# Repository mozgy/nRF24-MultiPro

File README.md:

# nRF24-MultiPro
nRF24 MultiPro

Adapter for nRF24 board and Arduino Pro Mini.
Firmware is at https://github.com/goebish/nrf24_multipro

# BOM
Qty|Part|Description|Value|Package|RS Part Number
---|----|-----------|-----|-------|-------------------
1|IC1|Voltage Regulator 3.3V|SPX3819 3.3|SOT23-5|
1|Q1|MOSFET|BSS123|SOT-23|
1|Q2|BJT|2N2222|SOT-23|
1|C1|Cap Tantalum|2.2uF/16V|3216|
2|R1,R2|SMD Resistor|10k|0805|
3|R3,R4,R5|SMD Resistor|1k|0805|
1|JP1|Pin Header|2x4|
2|JP2,JP3|Pin Header|1x12|
1|JP4|Molex Connector|1x5|

(C1 '+' cap markings are towards outter edge of the PCB)

Special thanks to excellent video by Jason Sanctuary - https://www.youtube.com/watch?v=gJYiDjo5lQw

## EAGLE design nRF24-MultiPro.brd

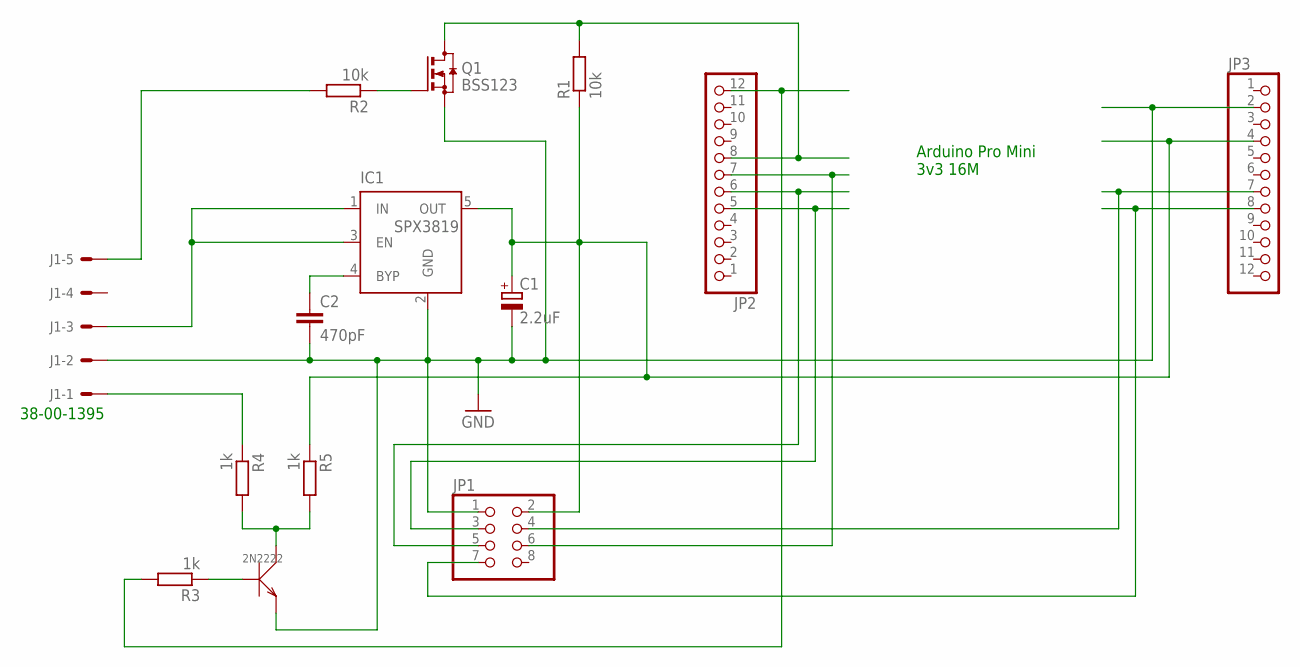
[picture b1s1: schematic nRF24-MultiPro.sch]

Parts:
2N2222: TRANSISTOR-NPN; SOT-23
C1: 2.2uF; A/3216-18W
C2: 470pF; C0805
IC1: SPX3819; SOT23-5
J1: 22-27-2051-05; 6410-05
JP1: PINHD-2X4; 2X04
JP2, JP3: PINHD-1X12; 1X12
Q1: BSS123; SOT23
R1, R2: 10k; R0805
R3, R4, R5: 1k; R0805

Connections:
GND: 2N2222.2 (E), C1.-, C2.2, IC1.2 (GND), J1.2, JP1.1, JP3.2, Q1.2 (S)
unnamed: IC1.1 (IN), IC1.3 (EN), J1.3
unnamed: JP2.8, Q1.3 (D), R1.2
unnamed: JP1.4, JP3.7
unnamed: C1.+, IC1.5 (OUT), JP1.2, JP3.4, R1.1, R5.1
unnamed: JP1.6, JP2.7
unnamed: 2N2222.1 (B), R3.1
unnamed: Q1.1 (G), R2.1
unnamed: J1.5, R2.2
unnamed: JP1.3, JP2.5
unnamed: JP1.5, JP2.6
unnamed: JP1.7, JP3.8
unnamed: 2N2222.3 (C), R4.2, R5.2
unnamed: J1.1, R4.1
unnamed: C2.1, IC1.4 (BYP)
unnamed: JP2.12, R3.2

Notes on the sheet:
Arduino Pro Mini 3v3 16M
38-00-1395

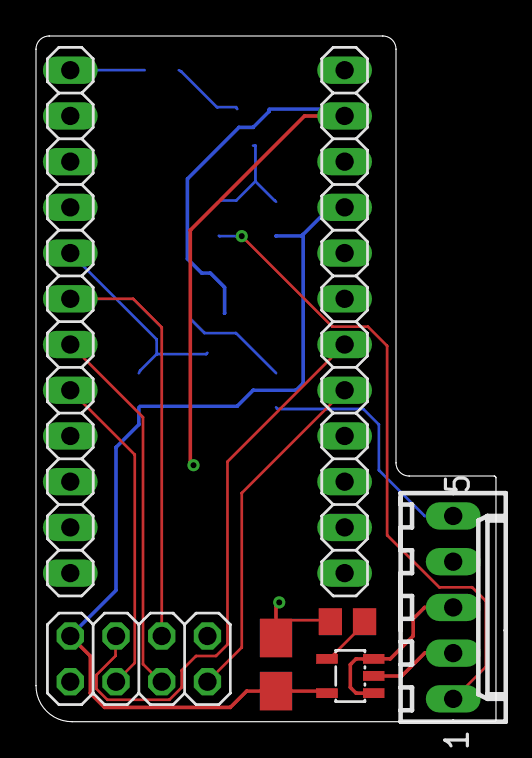
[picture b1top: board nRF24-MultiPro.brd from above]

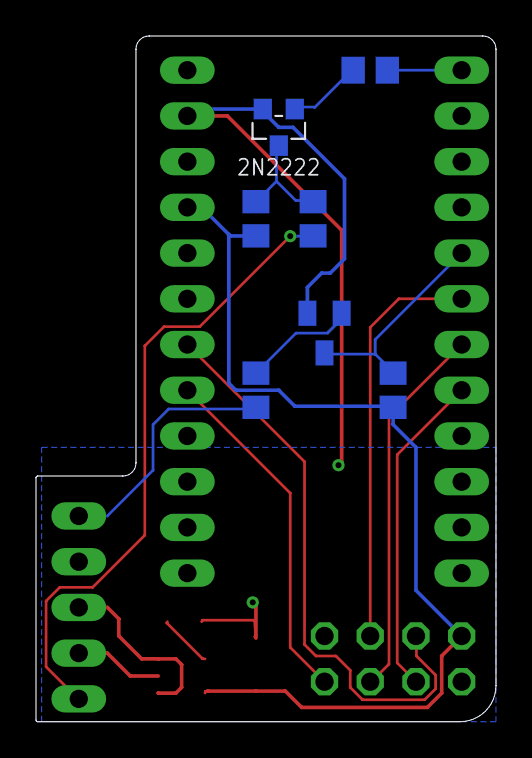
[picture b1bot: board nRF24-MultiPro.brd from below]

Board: 2 copper layers, 25.6 x 38.1 mm, 14 parts (7 on the bottom side), 16 nets.

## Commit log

2016-08-05 :neckbeard: Added .gitattributes & .gitignore files
2016-08-05 nRF24 MultiPro
    Adapter schematics for nRF24 board and Arduino Pro Mini, firmware at
    https://github.com/goebish/nrf24_multipro
2016-08-05 Schematics Picture
2016-08-08 OSH Park PCB
    OSH Park PCB
2016-08-08 v1.1 pcb
    - 470pF for low noise
    - slightly rearanged SMDs
    - manualy traced some wires
    - GND and VCC upped to 8mil
    - added logo
2016-09-06 3D Printer Data
    STLs for 3d printed box, 9xR version with antenae hole.
2016-10-30 Add C1 markings comment
2017-02-24 Add video link
2017-02-24 BOM
    Added BOM
